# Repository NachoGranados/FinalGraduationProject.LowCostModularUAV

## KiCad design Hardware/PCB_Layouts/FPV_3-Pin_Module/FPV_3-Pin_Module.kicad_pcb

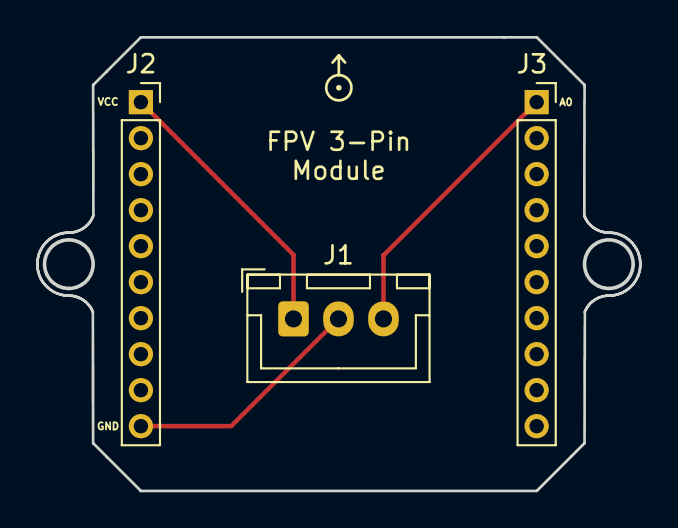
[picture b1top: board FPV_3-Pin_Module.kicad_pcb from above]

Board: 2 copper layers, 33.5 x 25.2 mm, 4 parts (0 on the bottom side), 3 nets.

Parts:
EXP_ORIENTATION: VAL**; EXP_ORIENTATION
J1: Conn_01x03_Socket; JST_XH_B3B-XH-A_1x03_P2.50mm_Vertical
J2, J3: Conn_01x10_Socket; PinSocket_1x10_P2.00mm_Vertical

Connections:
unnamed: J1.1, J2.1
unnamed: J1.2, J2.10
unnamed: J1.3, J3.1

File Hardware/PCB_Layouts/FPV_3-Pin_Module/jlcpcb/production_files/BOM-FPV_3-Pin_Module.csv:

Comment,Designator,Footprint,LCSC
Conn_01x03_Socket,J1,JST_XH_B3B-XH-A_1x03_P2.50mm_Vertical,
Conn_01x10_Socket,J2,PinSocket_1x10_P2.00mm_Vertical,
Conn_01x10_Socket,J3,PinSocket_1x10_P2.00mm_Vertical,

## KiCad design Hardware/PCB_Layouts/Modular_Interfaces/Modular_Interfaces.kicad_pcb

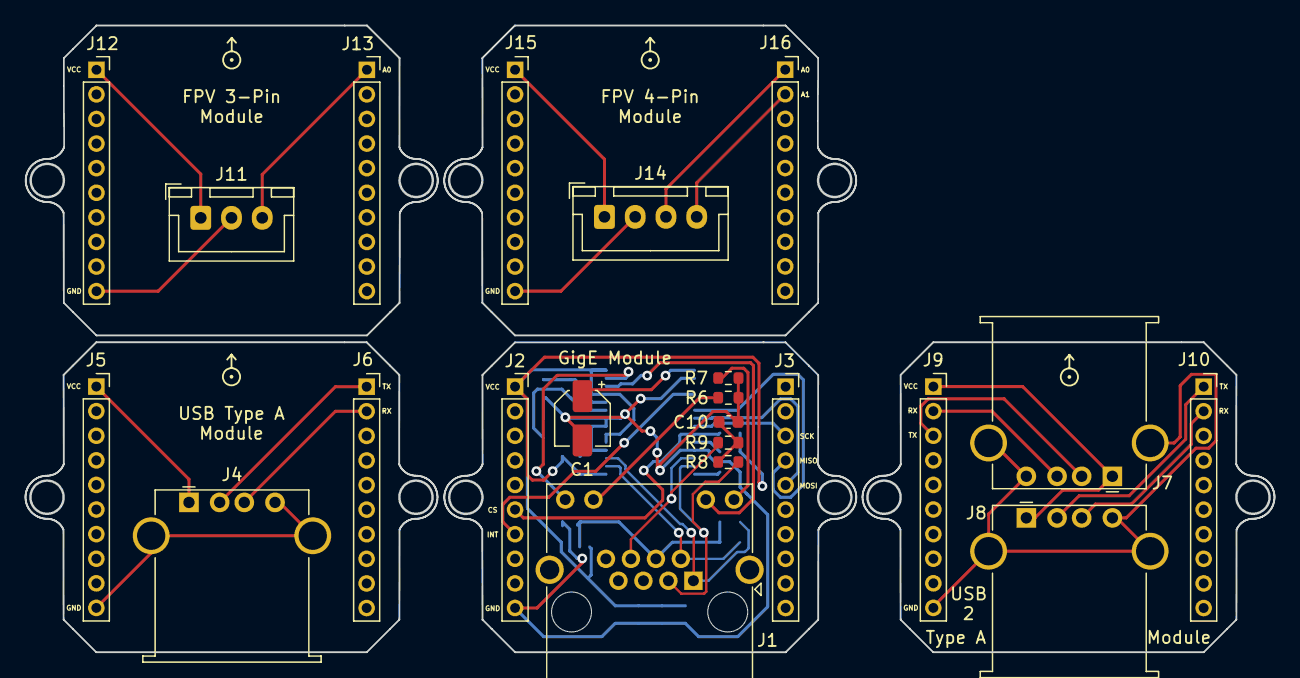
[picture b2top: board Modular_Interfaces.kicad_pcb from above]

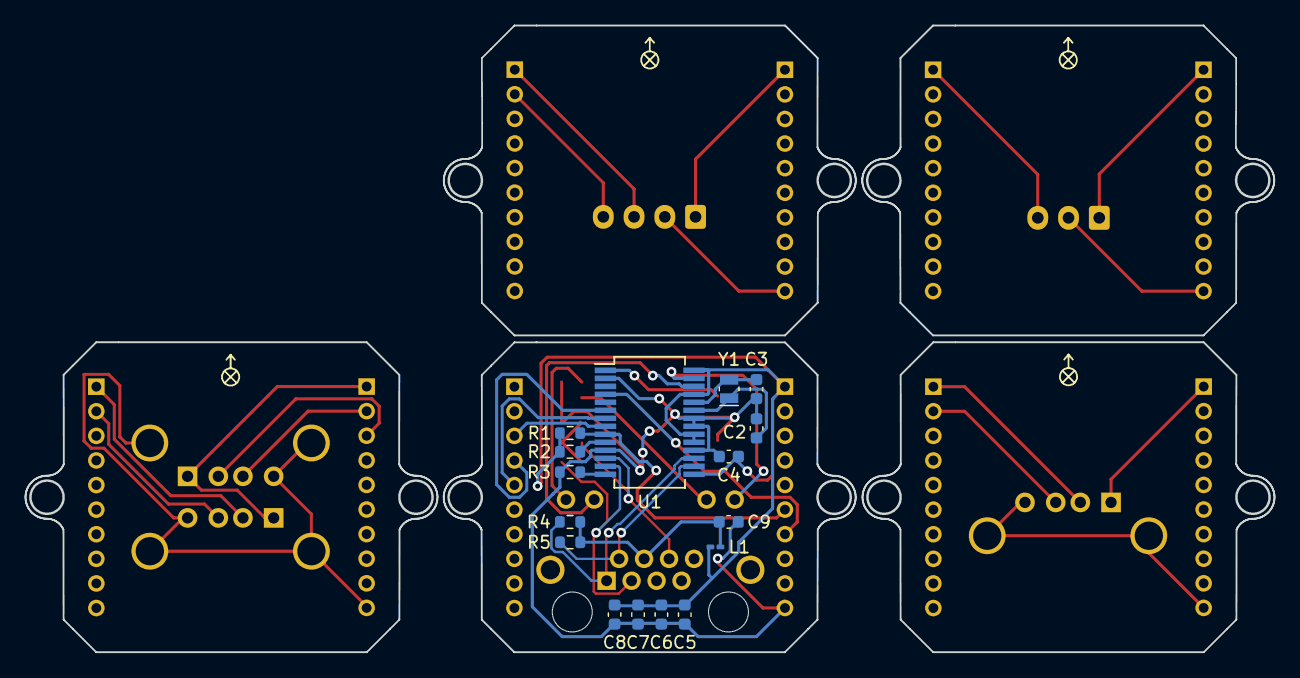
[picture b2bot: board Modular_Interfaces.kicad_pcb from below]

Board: 2 copper layers, 101.6 x 51.0 mm, 42 parts (16 on the bottom side), 39 nets.

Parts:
C1: 10uF; CP_Elec_4x5.4
C2, C3: 18pF; C_0603_1608Metric
C4, C5, C6, C7, C8, C9: 100nF; C_0603_1608Metric
C10: 10nF; C_0603_1608Metric
EXP_ORIENTATION: VAL**; EXP_ORIENTATION
EXP_ORIENTATION#2, EXP_ORIENTATION#3, EXP_ORIENTATION#4: VAL**; EXP_ORIENTATION
J1: RJ45_LED; RJ45_Amphenol_RJHSE538X
J2, J3, J5, J6, J9, J10, J12, J13, J15, J16: Conn_01x10_Socket; PinSocket_1x10_P2.00mm_Vertical
J4, J7, J8: USB_A; USB_A_Stewart_SS-52100-001_Horizontal
J11: Conn_01x03_Socket; JST_XH_B3B-XH-A_1x03_P2.50mm_Vertical
J14: Conn_01x04_Socket; JST_XH_B4B-XH-A_1x04_P2.50mm_Vertical
L1: 10uH; L_0201_0603Metric_Pad0.64x0.40mm_HandSolder
R1: 100k; R_0603_1608Metric
R2: 10k; R_0603_1608Metric
R3: 2k; R_0603_1608Metric
R4, R5, R8, R9: 49.9; R_0603_1608Metric
R6, R7: 180; R_0603_1608Metric
U1: ENC28J60x-SS; SSOP-28_5.3x10.2mm_P0.65mm
Y1: 25MHz; Crystal_SMD_MicroCrystal_CC8V-T1A-2Pin_2.0x1.2mm

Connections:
/CS: J2.6, R1.2, U1.9 (~CS)
/GND: C1.2, C2.1, C3.1, C4.2, C5.2, C6.2, C7.2, C8.2, C9.2, C10.2, J2.10, R3.2, R6.2, R7.2, U1.2 (VSS), U1.11 (VSSRX), U1.18 (VSSTX), U1.21 (VSSPLL), U1.22 (VSSOSC)
/INT: J2.7, U1.4 (~INT)
/LEDA: J1.12, U1.27 (LEDA)
/LEDB: J1.10, U1.26 (LEDB)
/MISO: J3.4, U1.6 (SO)
/MOSI: J3.5, U1.7 (SI)
/SCK: J3.3, U1.8 (SCK)
/TPIN+: J1.3, R8.2, U1.13 (TPIN+)
/TPIN-: J1.6, R9.1, U1.12 (TPIN-)
/TPOUT+: J1.1, R4.2, U1.17 (TPOUT+)
/TPOUT-: J1.2, R5.1, U1.16 (TPOUT-)
/VCC: C4.1, C5.1, C6.1, C7.1, C8.1, J2.1, L1.1, R1.1, R2.1, U1.15 (VDDTX), U1.19 (VDDRX), U1.20 (VDDPLL), U1.25 (VDDOSC), U1.28 (VDD)
unnamed: C9.1, J1.4, L1.2, R4.1, R5.2
unnamed: C10.1, R8.1, R9.2
unnamed: J1.9, R7.1
unnamed: J1.11, R6.1
unnamed: J4.3 (D+), J6.2
unnamed: J4.2 (D-), J6.1
unnamed: J4.4 (GND), J4.5 (Shield), J5.10
unnamed: J4.1 (VBUS), J5.1
unnamed: J7.3 (D+), J9.2
unnamed: J7.2 (D-), J9.3
unnamed: J7.4 (GND), J7.5 (Shield), J8.4 (GND), J8.5 (Shield), J9.10
unnamed: J7.1 (VBUS), J8.1 (VBUS), J9.1
unnamed: J8.2 (D-), J10.1
unnamed: J8.3 (D+), J10.2
unnamed: J11.1, J12.1
unnamed: J11.2, J12.10
unnamed: J11.3, J13.1
unnamed: J14.1, J15.1
unnamed: J14.2, J15.10
unnamed: J14.3, J16.1
unnamed: J14.4, J16.2
unnamed: C2.2, U1.23 (OSC1), Y1.1
unnamed: C3.2, U1.24 (OSC2), Y1.2
unnamed: R3.1, U1.14 (RBIAS)
unnamed: C1.1, U1.1 (VCAP)
unnamed: R2.2, U1.10 (~RESET)

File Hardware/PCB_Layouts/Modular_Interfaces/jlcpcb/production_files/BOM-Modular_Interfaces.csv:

Comment,Designator,Footprint,LCSC
Conn_01x10_Socket,J16,PinSocket_1x10_P2.00mm_Vertical,
Conn_01x10_Socket,J15,PinSocket_1x10_P2.00mm_Vertical,
Conn_01x04_Socket,J14,JST_XH_B4B-XH-A_1x04_P2.50mm_Vertical,
Conn_01x10_Socket,J6,PinSocket_1x10_P2.00mm_Vertical,
Conn_01x10_Socket,J10,PinSocket_1x10_P2.00mm_Vertical,
Conn_01x10_Socket,J5,PinSocket_1x10_P2.00mm_Vertical,
49.9,R8,R_0603_1608Metric,
Conn_01x10_Socket,J2,PinSocket_1x10_P2.00mm_Vertical,
10uF,C1,CP_Elec_4x5.4,
180,R6,R_0603_1608Metric,
Conn_01x10_Socket,J9,PinSocket_1x10_P2.00mm_Vertical,
Conn_01x10_Socket,J3,PinSocket_1x10_P2.00mm_Vertical,
USB_A,J8,USB_A_Stewart_SS-52100-001_Horizontal,
49.9,R9,R_0603_1608Metric,
USB_A,J4,USB_A_Stewart_SS-52100-001_Horizontal,
USB_A,J7,USB_A_Stewart_SS-52100-001_Horizontal,
Conn_01x03_Socket,J11,JST_XH_B3B-XH-A_1x03_P2.50mm_Vertical,
RJ45_LED,J1,RJ45_Amphenol_RJHSE538X,
180,R7,R_0603_1608Metric,
Conn_01x10_Socket,J13,PinSocket_1x10_P2.00mm_Vertical,
Conn_01x10_Socket,J12,PinSocket_1x10_P2.00mm_Vertical,
10nF,C10,C_0603_1608Metric,
100nF,C5,C_0603_1608Metric,
49.9,R5,R_0603_1608Metric,
100k,R1,R_0603_1608Metric,
10uH,L1,L_0201_0603Metric_Pad0.64x0.40mm_HandSolder,
10k,R2,R_0603_1608Metric,
25MHz,Y1,Crystal_SMD_MicroCrystal_CC8V-T1A-2Pin_2.0x1.2mm,
2k,R3,R_0603_1608Metric,
49.9,R4,R_0603_1608Metric,
100nF,C8,C_0603_1608Metric,
100nF,C6,C_0603_1608Metric,
100nF,C4,C_0603_1608Metric,
100nF,C9,C_0603_1608Metric,
18pF,C3,C_0603_1608Metric,
100nF,C7,C_0603_1608Metric,
ENC28J60x-SS,U1,SSOP-28_5.3x10.2mm_P0.65mm,
18pF,C2,C_0603_1608Metric,

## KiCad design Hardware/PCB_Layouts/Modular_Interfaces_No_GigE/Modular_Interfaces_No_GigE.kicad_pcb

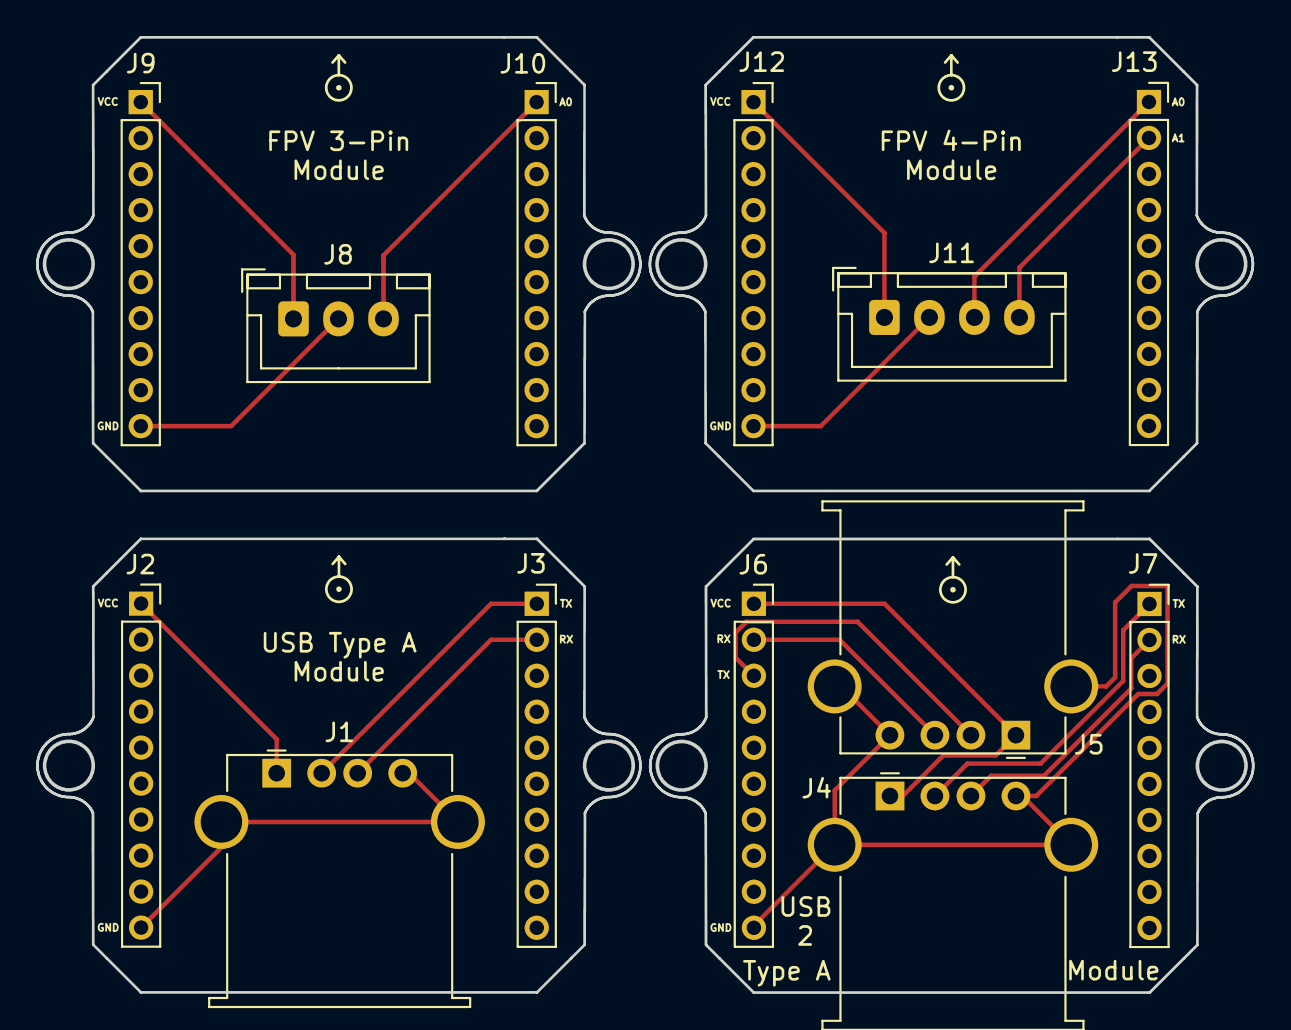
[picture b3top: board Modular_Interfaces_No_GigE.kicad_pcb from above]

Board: 2 copper layers, 67.5 x 53.1 mm, 17 parts (0 on the bottom side), 17 nets.

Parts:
EXP_ORIENTATION: VAL**; EXP_ORIENTATION
EXP_ORIENTATION#2, EXP_ORIENTATION#3, EXP_ORIENTATION#4: VAL**; EXP_ORIENTATION
J1, J4, J5: USB_A; USB_A_Stewart_SS-52100-001_Horizontal
J2, J3, J6, J7, J9, J10, J12, J13: Conn_01x10_Socket; PinSocket_1x10_P2.00mm_Vertical
J8: Conn_01x03_Socket; JST_XH_B3B-XH-A_1x03_P2.50mm_Vertical
J11: Conn_01x04_Socket; JST_XH_B4B-XH-A_1x04_P2.50mm_Vertical

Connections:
unnamed: J1.3 (D+), J3.2
unnamed: J1.2 (D-), J3.1
unnamed: J1.4 (GND), J1.5 (Shield), J2.10
unnamed: J1.1 (VBUS), J2.1
unnamed: J4.3 (D+), J6.2
unnamed: J4.2 (D-), J6.3
unnamed: J4.4 (GND), J4.5 (Shield), J5.4 (GND), J5.5 (Shield), J6.10
unnamed: J4.1 (VBUS), J5.1 (VBUS), J6.1
unnamed: J5.3 (D+), J7.2
unnamed: J5.2 (D-), J7.1
unnamed: J8.1, J9.1
unnamed: J8.2, J9.10
unnamed: J8.3, J10.1
unnamed: J11.1, J12.1
unnamed: J11.2, J12.10
unnamed: J11.3, J13.1
unnamed: J11.4, J13.2

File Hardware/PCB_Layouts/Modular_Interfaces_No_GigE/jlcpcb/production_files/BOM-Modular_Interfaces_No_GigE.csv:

Comment,Designator,Footprint,LCSC
Conn_01x04_Socket,J11,JST_XH_B4B-XH-A_1x04_P2.50mm_Vertical,
Conn_01x10_Socket,J13,PinSocket_1x10_P2.00mm_Vertical,
Conn_01x10_Socket,J12,PinSocket_1x10_P2.00mm_Vertical,
Conn_01x10_Socket,J10,PinSocket_1x10_P2.00mm_Vertical,
Conn_01x10_Socket,J9,PinSocket_1x10_P2.00mm_Vertical,
Conn_01x03_Socket,J8,JST_XH_B3B-XH-A_1x03_P2.50mm_Vertical,
Conn_01x10_Socket,J7,PinSocket_1x10_P2.00mm_Vertical,
Conn_01x10_Socket,J6,PinSocket_1x10_P2.00mm_Vertical,
USB_A,J5,USB_A_Stewart_SS-52100-001_Horizontal,
USB_A,J4,USB_A_Stewart_SS-52100-001_Horizontal,
Conn_01x10_Socket,J3,PinSocket_1x10_P2.00mm_Vertical,
Conn_01x10_Socket,J2,PinSocket_1x10_P2.00mm_Vertical,
USB_A,J1,USB_A_Stewart_SS-52100-001_Horizontal,

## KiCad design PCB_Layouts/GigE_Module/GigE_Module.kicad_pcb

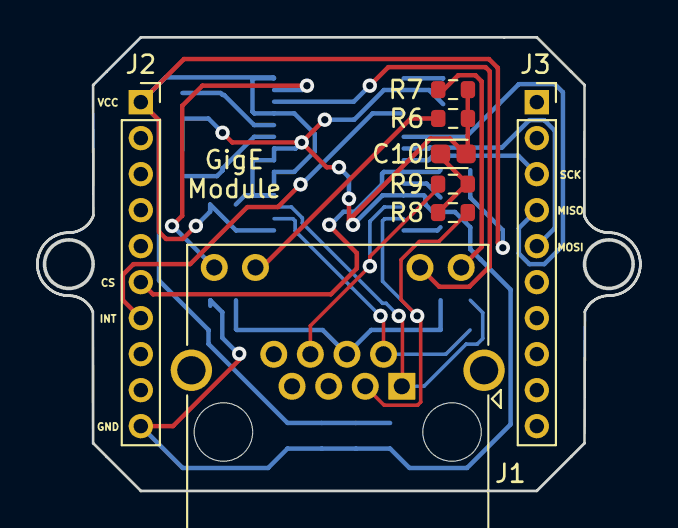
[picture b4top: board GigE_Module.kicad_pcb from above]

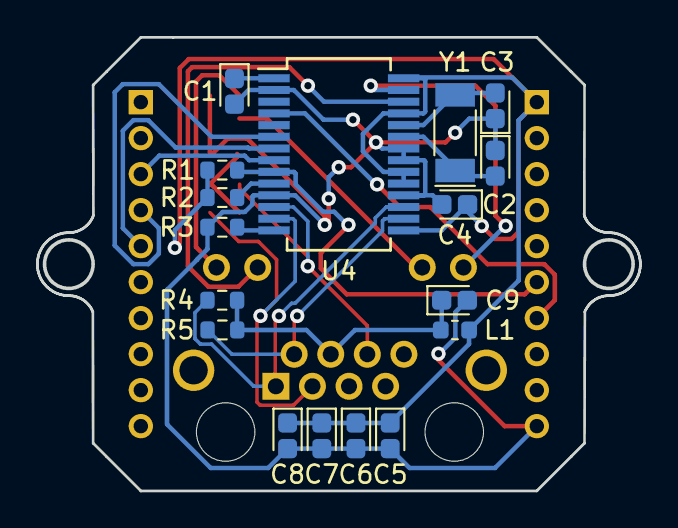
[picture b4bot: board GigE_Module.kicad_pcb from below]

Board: 2 copper layers, 33.5 x 25.2 mm, 25 parts (17 on the bottom side), 22 nets.

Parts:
C1: 10uF; CP_EIA-1608-08_AVX-J
C2, C3: 18pF; CP_EIA-1608-08_AVX-J
C4, C5, C6, C7, C8: 100nF; CP_EIA-1608-08_AVX-J
C9: 0.01u; CP_EIA-1608-08_AVX-J
C10: 10nF; CP_EIA-1608-08_AVX-J
J1: RJ45_LED; RJ45_Amphenol_RJHSE538X
J2, J3: Conn_01x10_Socket; PinSocket_1x10_P2.00mm_Vertical
L1: 10uH; L_0603_1608Metric
R1: 100k; R_0603_1608Metric
R2: 10k; R_0603_1608Metric
R3: 2k; R_0603_1608Metric
R4, R5, R8, R9: 49.9; R_0603_1608Metric
R6, R7: 180; R_0603_1608Metric
U4: ENC28J60x-SS; SSOP-28_5.3x10.2mm_P0.65mm
Y1: 25MHz; Crystal_SMD_MicroCrystal_CC4V-T1A-2Pin_5.0x1.9mm

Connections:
/CS: J2.6, R1.2, U4.9 (~CS)
/GND: C1.2, C2.1, C3.1, C4.2, C5.2, C6.2, C7.2, C8.2, C9.2, C10.2, J2.10, R3.2, R6.2, R7.2, U4.2 (VSS), U4.11 (VSSRX), U4.18 (VSSTX), U4.21 (VSSPLL), U4.22 (VSSOSC)
/INT: J2.7, U4.4 (~INT)
/LEDA: J1.12, U4.27 (LEDA)
/LEDB: J1.10, U4.26 (LEDB)
/MISO: J3.4, U4.6 (SO)
/MOSI: J3.5, U4.7 (SI)
/SCK: J3.3, U4.8 (SCK)
/TPIN+: J1.3, R8.2, U4.13 (TPIN+)
/TPIN-: J1.6, R9.1, U4.12 (TPIN-)
/TPOUT+: J1.1, R4.2, U4.17 (TPOUT+)
/TPOUT-: J1.2, R5.1, U4.16 (TPOUT-)
/VCC: C4.1, C5.1, C6.1, C7.1, C8.1, J2.1, L1.1, R1.1, R2.1, U4.15 (VDDTX), U4.19 (VDDRX), U4.20 (VDDPLL), U4.25 (VDDOSC), U4.28 (VDD)
unnamed: C9.1, J1.4, L1.2, R4.1, R5.2
unnamed: C10.1, R8.1, R9.2
unnamed: J1.9, R7.1
unnamed: J1.11, R6.1
unnamed: C2.2, U4.23 (OSC1), Y1.1
unnamed: C3.2, U4.24 (OSC2), Y1.2
unnamed: R3.1, U4.14 (RBIAS)
unnamed: C1.1, U4.1 (VCAP)
unnamed: R2.2, U4.10 (~RESET)

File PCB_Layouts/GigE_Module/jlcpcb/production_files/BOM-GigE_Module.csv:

Comment,Designator,Footprint,LCSC
RJ45_LED,J1,RJ45_Amphenol_RJHSE538X,
180,R7,R_0603_1608Metric,
180,R6,R_0603_1608Metric,
49.9,R9,R_0603_1608Metric,
Conn_01x10_Socket,J3,PinSocket_1x10_P2.00mm_Vertical,
Conn_01x10_Socket,J2,PinSocket_1x10_P2.00mm_Vertical,
10nF,C10,CP_EIA-1608-08_AVX-J,
49.9,R8,R_0603_1608Metric,
10k,R2,R_0603_1608Metric,
ENC28J60x-SS,U4,SSOP-28_5.3x10.2mm_P0.65mm,
100nF,C7,CP_EIA-1608-08_AVX-J,
100nF,C6,CP_EIA-1608-08_AVX-J,
49.9,R5,R_0603_1608Metric,
18pF,C3,CP_EIA-1608-08_AVX-J,
10uH,L1,L_0603_1608Metric,
100nF,C8,CP_EIA-1608-08_AVX-J,
49.9,R4,R_0603_1608Metric,
18pF,C2,CP_EIA-1608-08_AVX-J,
100k,R1,R_0603_1608Metric,
25MHz,Y1,Crystal_SMD_MicroCrystal_CC4V-T1A-2Pin_5.0x1.9mm,
100nF,C4,CP_EIA-1608-08_AVX-J,
100nF,C5,CP_EIA-1608-08_AVX-J,
10uF,C1,CP_EIA-1608-08_AVX-J,
0.01u,C9,CP_EIA-1608-08_AVX-J,
2k,R3,R_0603_1608Metric,

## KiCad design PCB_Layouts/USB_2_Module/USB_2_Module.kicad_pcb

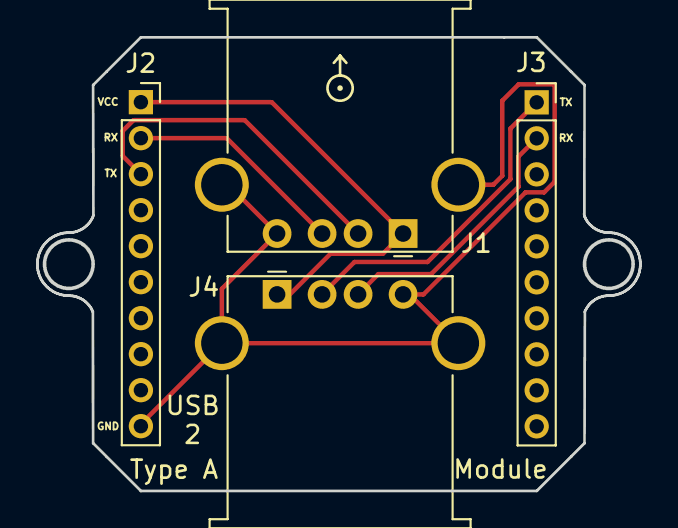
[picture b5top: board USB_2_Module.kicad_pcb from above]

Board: 2 copper layers, 33.5 x 25.2 mm, 5 parts (0 on the bottom side), 6 nets.

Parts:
EXP_ORIENTATION: VAL**; EXP_ORIENTATION
J1, J4: USB_A; USB_A_Stewart_SS-52100-001_Horizontal
J2, J3: Conn_01x10_Socket; PinSocket_1x10_P2.00mm_Vertical

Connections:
unnamed: J1.3 (D+), J2.2
unnamed: J1.2 (D-), J2.3
unnamed: J1.4 (GND), J1.5 (Shield), J2.10, J4.4 (GND), J4.5 (Shield)
unnamed: J1.1 (VBUS), J2.1, J4.1 (VBUS)
unnamed: J3.1, J4.2 (D-)
unnamed: J3.2, J4.3 (D+)
